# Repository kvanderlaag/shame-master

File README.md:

# shame-master
A depressing clone of the Creative Labs CT-1300B Game Blaster

TODO:
- Explain what the shit this stupid thing does
- Explain all the ways in which it is bad
- Explain the differences from the original Game Blaster
- Add a bill of materials

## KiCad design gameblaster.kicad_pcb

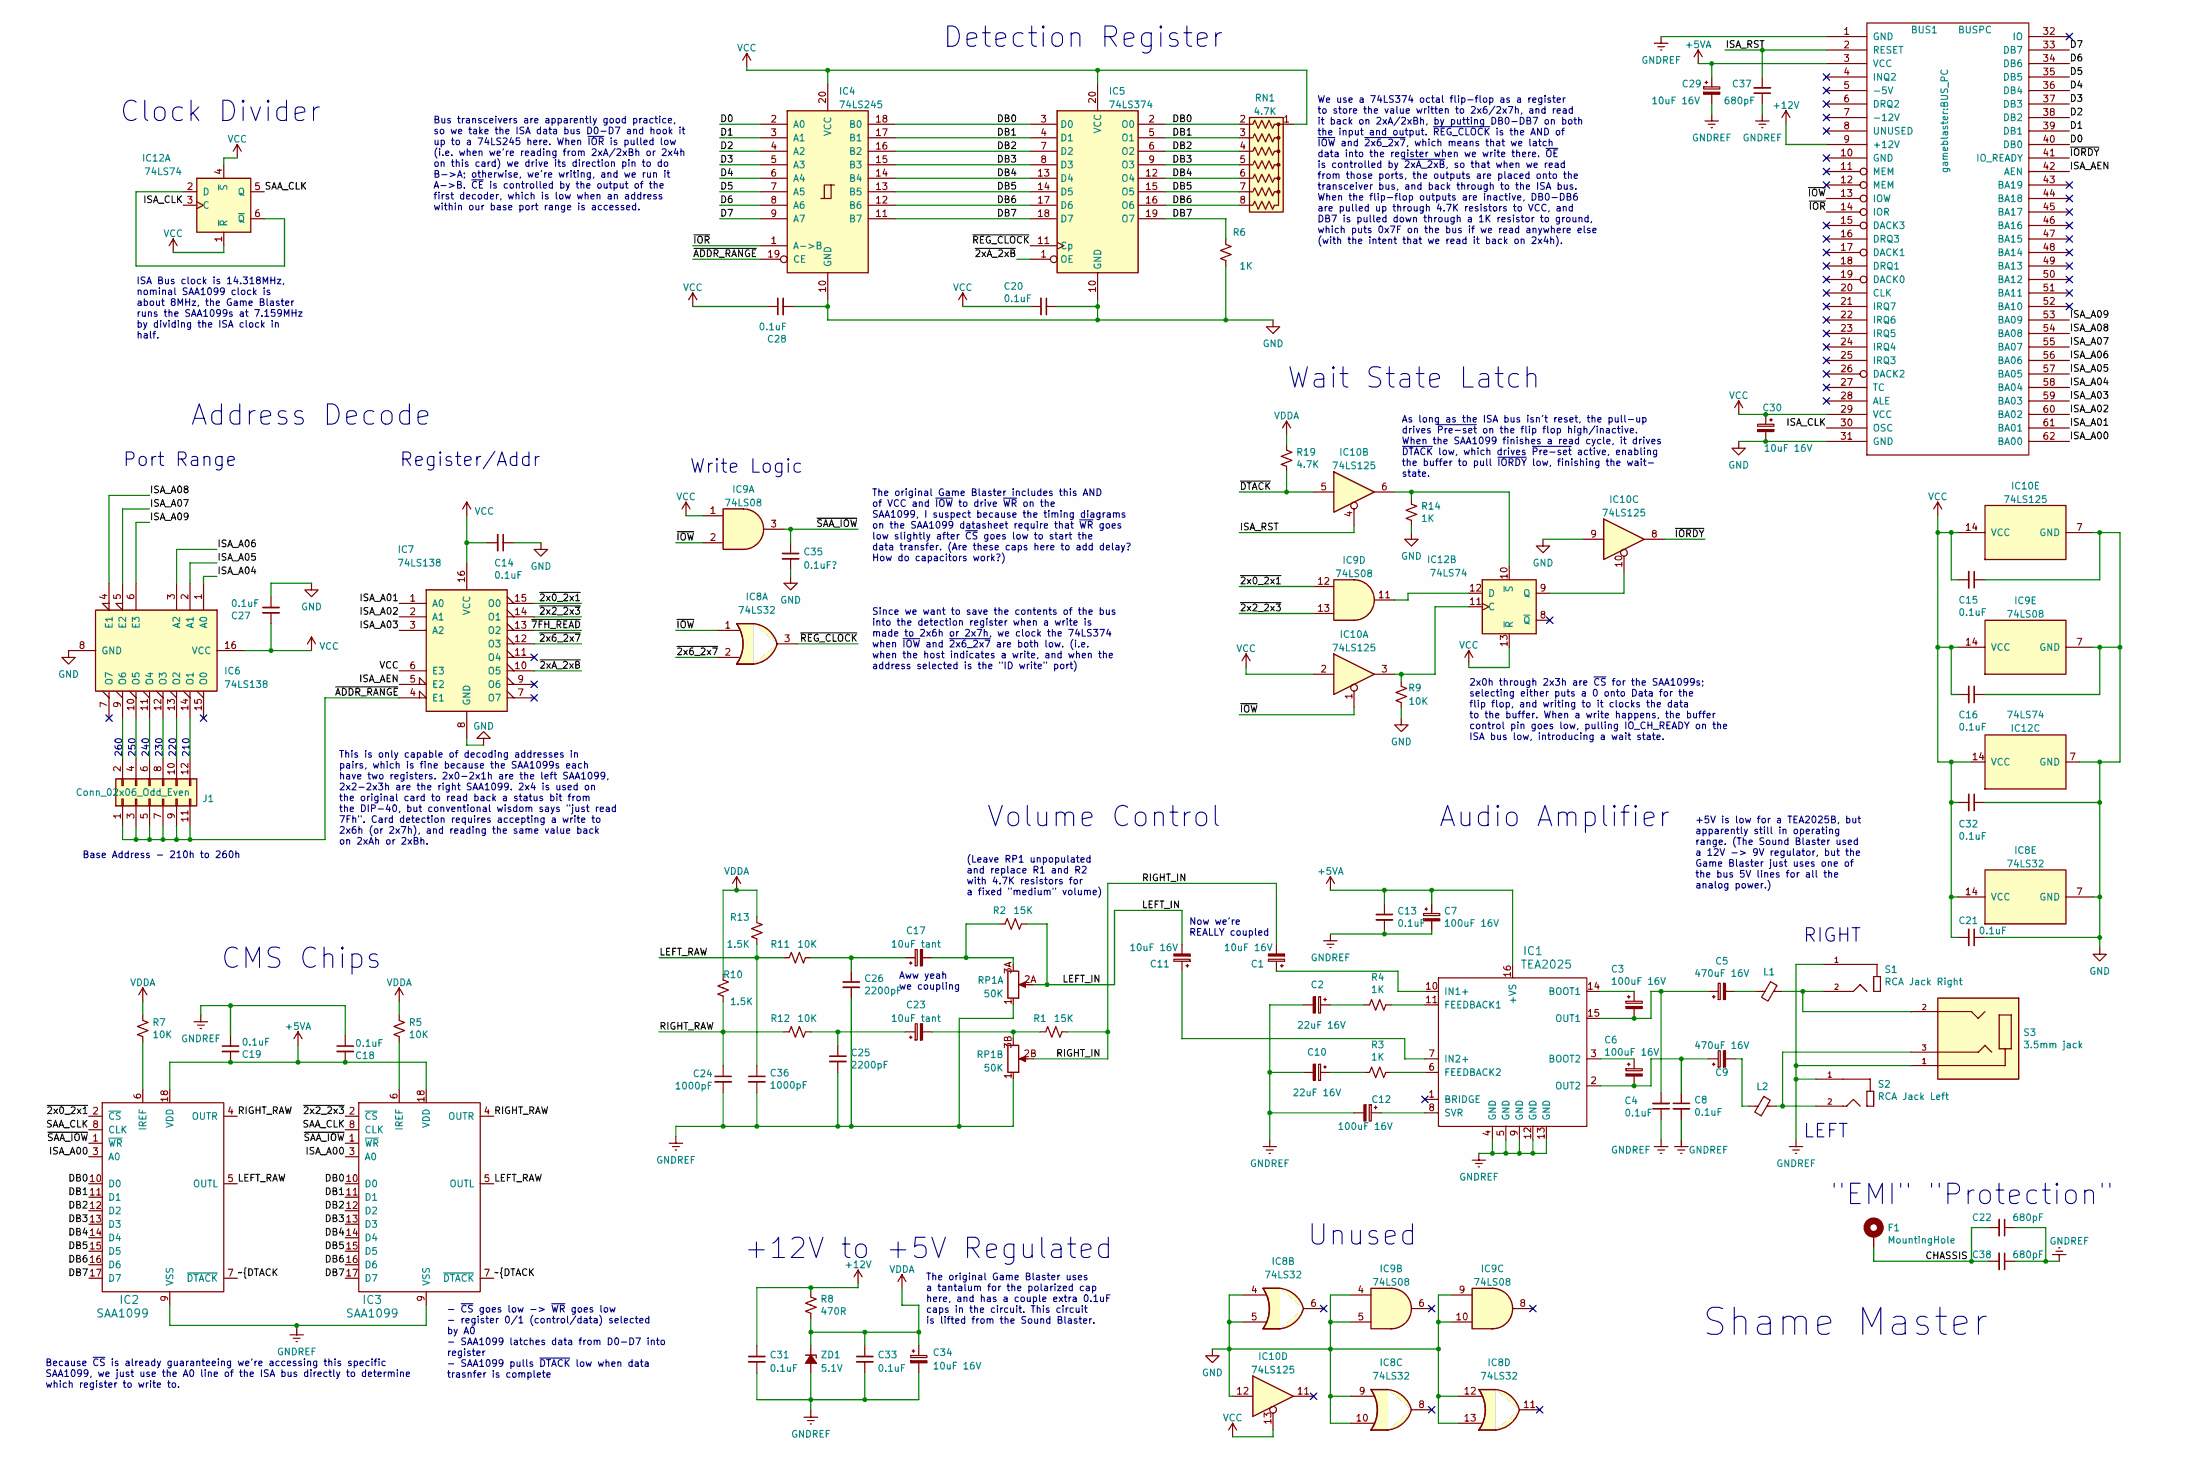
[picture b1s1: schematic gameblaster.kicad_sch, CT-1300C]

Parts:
BUS1: BUSPC; BUS_PC
C1, C11, C29, C30, C34: 10uF 16V; CAPAP100
C2, C10: 22uF 16V; CAPAP100
C3, C6, C7, C12: 100uF 16V; CAPAP200
C4, C8, C13, C14, C15, C16, C18, C19, C20, C21, C27, C28, C31, C32, C33: 0.1uF; CAPAC200
C5, C9: 470uF 16V; CAPAP200
C17, C23: 10uF tant; CAPAP100; DigiKey 478-11561-1-ND
C22, C37, C38: 680pF; CAPAC200
C24, C36: 1000pF; CAPAC200
C25, C26: 2200pF; CAPAC200
C35: 0.1uF?; CAPAC200
F1: MountingHole; MNT_KEYSTONE_9202
IC1: TEA2025; DIP254P762X635-16
IC2, IC3: SAA1099; DIP254P762X635-18
IC4: 74LS245; DIP254P762X635-20
IC5: 74LS374; DIP254P762X635-20
IC6, IC7: 74LS138; DIP254P762X635-16
IC8: 74LS32; DIP254P762X635-14
IC9: 74LS08; DIP254P762X635-14
IC10: 74LS125; DIP254P762X635-14
IC12: 74LS74; DIP254P762X635-14
J1: Conn_02x06_Odd_Even; SB_HDR_2X6
L1, L2: Ferrite_Bead_Small; INDA500P780X750
R1, R2: 15K; RESA400
R3, R4, R6, R14: 1K; RESA400
R5, R7, R9, R11, R12: 10K; RESA400
R8: 470R; RESA400
R10, R13: 1.5K; RESA400
R19: 4.7K; RESA400
RN1: 4.7K; R_Array_SIP8
RP1: 50K; GB_BOURNS_PDB08-DUAL
S1: RCA Jack Right; CUI_RCJ-042
S2: RCA Jack Left; CUI_RCJ-043
S3: 3.5mm jack; CUI_SJ1-3553NG
ZD1: 5.1V; DIOA400

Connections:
+5VA: BUS1.3 (VCC), C7.1, C13.1, C18.2, C19.2, C29.1, IC1.16 (+VS), IC2.18 (VDD), IC3.18 (VDD)
+12V: BUS1.9 (+12V), C31.1, R8.1
/CHASSIS: C22.2, C38.2, F1.1
/D0: BUS1.40 (DB0), IC4.2 (A0)
/D1: BUS1.39 (DB1), IC4.3 (A1)
/D2: BUS1.38 (DB2), IC4.4 (A2)
/D3: BUS1.37 (DB3), IC4.5 (A3)
/D4: BUS1.36 (DB4), IC4.6 (A4)
/D5: BUS1.35 (DB5), IC4.7 (A5)
/D6: BUS1.34 (DB6), IC4.8 (A6)
/D7: BUS1.33 (DB7), IC4.9 (A7)
/DB0: IC2.10 (D0), IC3.10 (D0), IC4.18 (B0), IC5.2 (O0), IC5.3 (D0), RN1.2 (R1)
/DB1: IC2.11 (D1), IC3.11 (D1), IC4.17 (B1), IC5.4 (D1), IC5.5 (O1), RN1.3 (R2)
/DB2: IC2.12 (D2), IC3.12 (D2), IC4.16 (B2), IC5.6 (O2), IC5.7 (D2), RN1.4 (R3)
/DB3: IC2.13 (D3), IC3.13 (D3), IC4.15 (B3), IC5.8 (D3), IC5.9 (O3), RN1.5 (R4)
/DB4: IC2.14 (D4), IC3.14 (D4), IC4.14 (B4), IC5.12 (O4), IC5.13 (D4), RN1.6 (R5)
/DB5: IC2.15 (D5), IC3.15 (D5), IC4.13 (B5), IC5.14 (D5), IC5.15 (O5), RN1.7 (R6)
/DB6: IC2.16 (D6), IC3.16 (D6), IC4.12 (B6), IC5.16 (O6), IC5.17 (D6), RN1.8 (R7)
/DB7: IC2.17 (D7), IC3.17 (D7), IC4.11 (B7), IC5.18 (D7), IC5.19 (O7), R6.1
/ISA_A00: BUS1.62 (BA00), IC2.3 (A0), IC3.3 (A0)
/ISA_A01: BUS1.61 (BA01), IC7.1 (A0)
/ISA_A02: BUS1.60 (BA02), IC7.2 (A1)
/ISA_A03: BUS1.59 (BA03), IC7.3 (A2)
/ISA_A04: BUS1.58 (BA04), IC6.1 (A0)
/ISA_A05: BUS1.57 (BA05), IC6.2 (A1)
/ISA_A06: BUS1.56 (BA06), IC6.3 (A2)
/ISA_A07: BUS1.55 (BA07), IC6.5 (E2)
/ISA_A08: BUS1.54 (BA08), IC6.4 (E1)
/ISA_A09: BUS1.53 (BA09), IC6.6 (E3)
/ISA_AEN: BUS1.42 (AEN), IC7.5 (E2)
/ISA_CLK: BUS1.30 (OSC), IC12.3 (C)
/ISA_RST: BUS1.2 (RESET), C37.2, IC10.4
/LEFT_IN: C11.2, R2.2, RP1.2A
/LEFT_RAW: C36.1, IC2.5 (OUTL), IC3.5 (OUTL), R11.1, R13.1
/RIGHT_IN: C1.2, R1.2, RP1.2B
/RIGHT_RAW: C24.1, IC2.4 (OUTR), IC3.4 (OUTR), R10.1, R12.1
/SAA_CLK: IC2.8 (CLK), IC3.8 (CLK), IC12.5 (Q)
/~2x0_2x1: IC2.2 (~CS), IC7.15 (O0), IC9.12
/~2x2_2x3: IC3.2 (~CS), IC7.14 (O1), IC9.13
/~2x6_2x7: IC7.12 (O3), IC8.2
/~2xA_2xB: IC5.1 (OE), IC7.10 (O5)
/~7FH_READ: IC7.13 (O2)
/~ADDR_RANGE: IC4.19 (CE), IC7.4 (E1), J1.1, J1.3, J1.5, J1.7, J1.9, J1.11
/~IORDY: BUS1.41 (IO_READY), IC10.8
/~IOR: BUS1.14 (IOR), IC4.1 (A->B)
/~IOW: BUS1.13 (IOW), IC8.1, IC9.2, IC10.1
/~REG_CLOCK: IC5.11 (Cp), IC8.3
/~SAA_IOW: C35.1, IC2.1 (~WR), IC3.1 (~WR), IC9.3
GND: BUS1.31 (GND), C14.1, C15.1, C16.1, C20.1, C21.1, C27.1, C28.2, C30.2, C32.1, C35.2, IC4.10 (GND), IC5.10 (GND), IC6.8 (GND), IC7.8 (GND), IC8.4, IC8.5, IC8.7 (GND), IC8.9, IC8.10, IC8.12, IC8.13, IC9.4, IC9.5, IC9.7 (GND), IC9.9, IC9.10, IC10.7 (GND), IC10.9, IC10.12, IC12.7 (GND), R6.2, R9.2, R14.2
GNDREF: BUS1.1 (GND), C2.2, C4.1, C7.2, C8.2, C10.2, C12.2, C13.2, C18.1, C19.1, C22.1, C24.2, C25.2, C26.2, C29.2, C31.2, C33.2, C34.2, C36.2, C37.1, C38.1, IC1.4 (GND), IC1.5 (GND), IC1.9 (GND), IC1.12 (GND), IC1.13 (GND), IC2.9 (VSS), IC3.9 (VSS), RP1.1, S1.1, S2.1, S3.1, ZD1.2 (A)
unnamed: C1.1, IC1.10 (IN1+)
unnamed: C2.1, R4.2
unnamed: C3.1, IC1.14 (BOOT1)
unnamed: C3.2, C4.2, C5.1, IC1.15 (OUT1)
unnamed: C5.2, L1.2
unnamed: C6.1, IC1.3 (BOOT2)
unnamed: C6.2, C8.1, C9.1, IC1.2 (OUT2)
unnamed: C9.2, L2.2
unnamed: C10.1, R3.2
unnamed: C11.1, IC1.7 (IN2+)
unnamed: C12.1, IC1.8 (SVR)
unnamed: C17.1, C26.1, R11.2
unnamed: C17.2, R2.1, RP1.3A
unnamed: C23.1, C25.1, R12.2
unnamed: C23.2, R1.1, RP1.3B
unnamed: IC1.6 (FEEDBACK2), R3.1
unnamed: IC1.11 (FEEDBACK1), R4.1
unnamed: IC2.6 (IREF), R7.2
unnamed: IC3.6 (IREF), R5.2
unnamed: IC6.9 (O6), J1.2
unnamed: IC6.10 (O5), J1.4
unnamed: IC6.11 (O4), J1.6
unnamed: IC6.12 (O3), J1.8
unnamed: IC6.13 (O2), J1.10
unnamed: IC6.14 (O1), J1.12
unnamed: IC10.3, IC12.11 (C), R9.1
unnamed: IC10.6, IC12.10 (~S), R14.1
unnamed: IC10.10, IC12.9 (Q)
unnamed: IC12.2 (D), IC12.6 (~Q)
unnamed: IC9.11, IC12.12 (D)
unnamed: L1.1, S1.2, S3.2
unnamed: L2.1, S2.2, S3.3
VCC: BUS1.29 (VCC), C14.2, C15.2, C16.2, C20.2, C21.2, C27.2, C28.1, C30.1, C32.2, IC4.20 (VCC), IC5.20 (VCC), IC6.16 (VCC), IC7.6 (E3), IC7.16 (VCC), IC8.14 (VCC), IC9.1, IC9.14 (VCC), IC10.2, IC10.13, IC10.14 (VCC), IC12.1 (~R), IC12.4 (~S), IC12.13 (~R), IC12.14 (VCC), RN1.1 (common)
VDDA: C33.1, C34.1, R5.1, R7.1, R8.2, R10.2, R13.2, R19.1, ZD1.1 (K)

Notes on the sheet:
Register/Addr
Port Range
Write Logic
+5V is low for a TEA2025B, but apparently still in operating range. (The Sound Blaster used a 12V -> 9V regulator, but the Game Blaster just uses one of the bus 5V lines for all the analog power.)
This is only capable of decoding addresses in pairs, which is fine because the SAA1099s each have two registers. 2x0-2x1h are the left SAA1099, 2x2-2x3h are the right SAA1099. 2x4 is used on the original card to read back a status bit from the DIP-40, but conventional wisdom says "just read 7Fh". C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
ISA Bus clock is 14.318MHz, nominal SAA1099 clock is about 8MHz, the Game Blaster runs the SAA1099s at 7.159MHz by dividing the ISA clock in half.
Wait State Latch
Detection Register
Shame Master
The original Game Blaster uses a tantalum for the polarized cap here, and has a couple extra 0.1uF caps in the circuit. This circuit is lifted from the Sound Blaster.
Bus transceivers are apparently good practice, so we take the ISA data bus D0-D7 and hook it up to a 74LS245 here. When ~{IOR} is pulled low (i.e. when we're reading from 2xA/2xBh or 2x4h on this card) we drive its direction pin to do B->A; otherwise, we're writing, and we run it A->B. ~{CE} is con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
230
"EMI" "Protection"
Volume Control
+12V to +5V Regulated
Since we want to save the contents of the bus into the detection register when a write is made to 2x6h or 2x7h, we clock the 74LS374 when ~{IOW} and ~{2x6_2x7} are both low. (i.e. when the host indicates a write, and when the address selected is the "ID write" port)
Address Decode
Base Address - 210h to 260h
220
We use a 74LS374 octal flip-flop as a register to store the value written to 2x6/2x7h, and read it back on 2xA/2xBh, by putting DB0-DB7 on both the input and output. ~{REG_CLOCK} is the AND of ~{IOW} and ~{2x6_2x7}, which means that we latch data into the register when we write there. ~{OE} is cont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
LEFT
2x0h through 2x3h are ~{CS} for the SAA1099s; selecting either puts a 0 onto Data for the flip flop, and writing to it clocks the data to the buffer. When a write happens, the buffer control pin goes low, pulling IO_CH_READY on the ISA bus low, introducing a wait state.
RIGHT
210
250
Because ~{CS} is already guaranteeing we're accessing this specific SAA1099, we just use the A0 line of the ISA bus directly to determine which register to write to.
240
(Leave RP1 unpopulated and replace R1 and R2 with 4.7K resistors for a fixed "medium" volume)
The original Game Blaster includes this AND of VCC and ~{IOW} to drive ~{WR} on the SAA1099, I suspect because the timing diagrams on the SAA1099 datasheet require that ~{WR} goes low slightly after ~{CS} goes low to start the data transfer. (Are these caps here to add delay? How do capacitors work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
As long as the ISA bus isn't reset, the pull-up drives ~{Pre-set} on the flip flop high/inactive. When the SAA1099 finishes a read cycle, it drives ~{DTACK} low, which drives ~{Pre-set} active, enabling the buffer to pull ~{IORDY} low, finishing the wait- state.
Now we're REALLY coupled
Clock Divider
- ~{CS} goes low -> ~{WR} goes low - register 0/1 (control/data) selected by A0 - SAA1099 latches data from D0-D7 into register - SAA1099 pulls ~{DTACK} low when data trasnfer is complete
CMS Chips
Audio Amplifier
260
Unused
Aww yeah we coupling

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
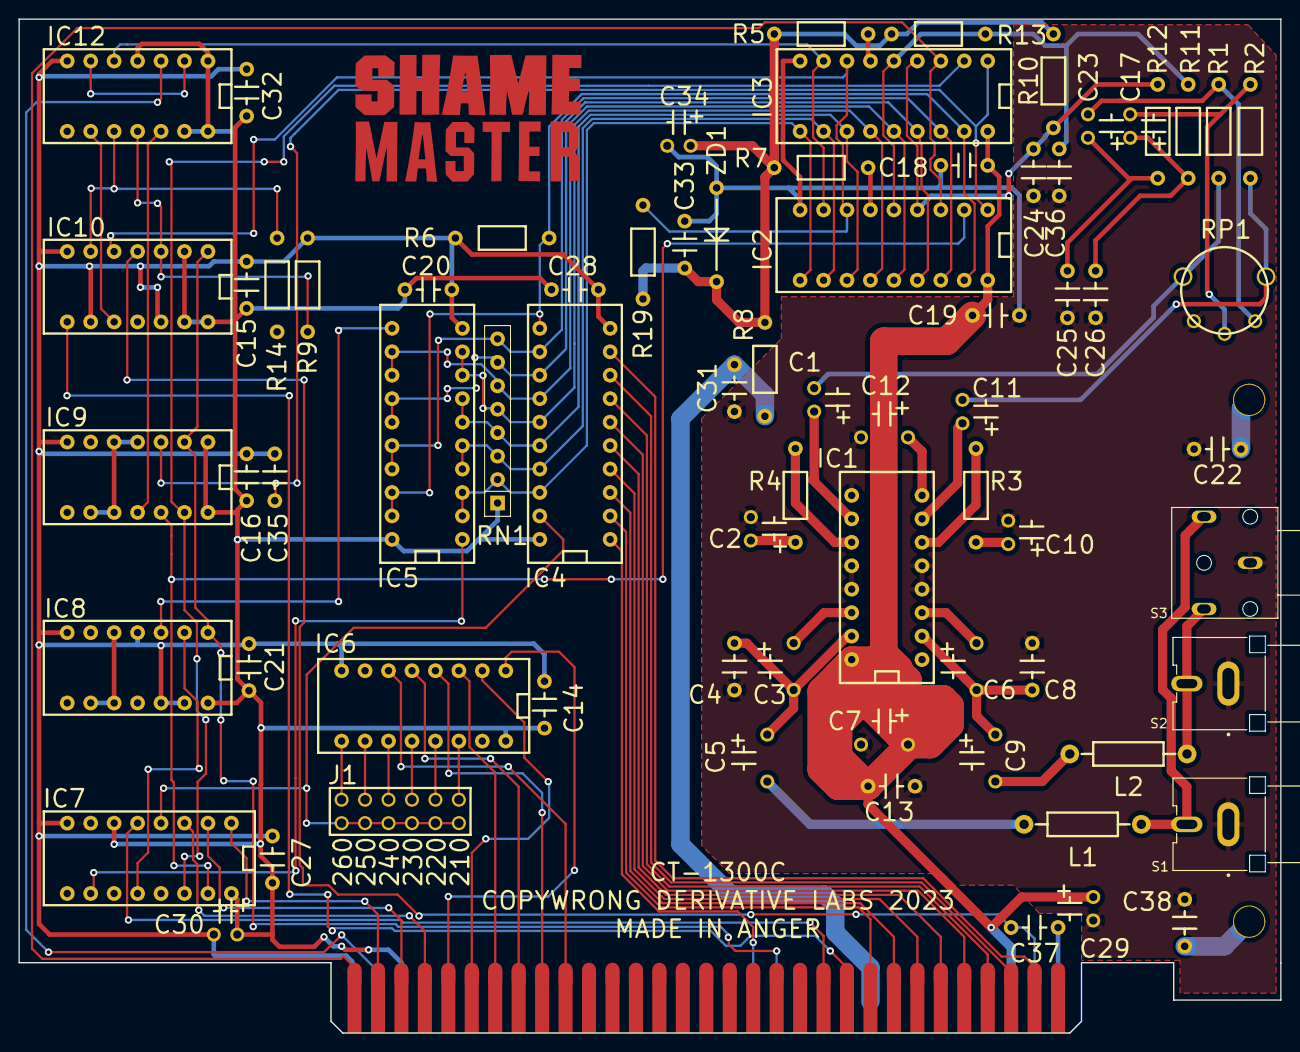
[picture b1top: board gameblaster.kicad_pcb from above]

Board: 2 copper layers, 136.7 x 109.8 mm, 75 parts (0 on the bottom side), 84 nets.

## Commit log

2023-02-08 rev 0
    who knows if this works? let's find out!
2023-02-08 add zener regulator for SAA1099s
2023-02-08 moved R6 because i like the way this looks better
2023-02-08 added some 3d crap, moved some components around to fit
2023-02-08 add logo, engorge zones, clip solder mask from card fingers
2023-02-08 update gerbil
2023-02-16 so much dumb shit
2023-02-16 dumb schematic shit
2023-02-17 heavily annotate schematic
2023-02-17 Separate +5VA and VDDA; re-add SAA1099 output current source; use power symbols
2023-02-17 updated board
    yes i know the left ICs are misaligned
2023-02-17 update pdf
2023-02-17 realign IC7 through IC11
2023-02-17 fuck it let's add a big old digital ground plane
2023-03-04 Fix some shit
2023-03-15 Add 3D models for Bracket and Volume pot/knob, update gerbers
